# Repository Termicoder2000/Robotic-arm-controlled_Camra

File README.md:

# Robotic Arm Controlled Camera

A Raspberry Pi camera tracks a face and moves a servo-driven robotic arm to keep that face in view. The Raspberry Pi performs camera capture and face detection; an Arduino receives movement commands over I2C and generates the servo PWM signals.

## System Overview

1. The Raspberry Pi captures 640 x 480 camera frames and detects faces with OpenCV.
2. If several faces are visible, it selects the face closest to the previously tracked face.
3. It calculates the selected face's horizontal and vertical offset from the image center.
4. It sends each direction and magnitude to the Arduino over I2C (slave address `0x50`).
5. The Arduino updates hardware timer values to move the servos. A button connected to Raspberry Pi BCM GPIO 21 requests a system shutdown.

### Raspberry Pi Flow

### Arduino Flow

## Why Use an Arduino for Servo PWM?

The Raspberry Pi runs Linux, a multitasking operating system that does not guarantee when a user-space process will run. If software on the Pi bit-bangs servo PWM through GPIO, scheduling delays can shift pulse edges and introduce timing jitter. Servos may respond to that jitter with audible noise, vibration, or imprecise movement.

The Arduino handles the time-critical servo pulses using its hardware timers. Timer peripherals continue producing regular PWM independently of the main program's I2C processing. This separates the Pi's demanding camera and computer-vision work from the precise timing needed to control the servos. The Pi can generate hardware PWM on some pins and configurations, but this project uses the Arduino's timer-driven outputs for servo control.

## Hardware

- Raspberry Pi with a compatible camera module
- Arduino-compatible controller and the servo-control circuit
- Servo-driven robotic arm
- I2C connection between the Raspberry Pi and Arduino
- Momentary shutdown button connected to BCM GPIO 21 and ground

The project photo below shows the custom controller board mounted above the Raspberry Pi.

**Electrical note:** Raspberry Pi GPIO is 3.3 V only. Make sure the I2C bus pull-ups are safe for the Raspberry Pi; use a bidirectional logic-level shifter if the Arduino side pulls the bus up to 5 V. Connect the grounds of both boards.

## Software

The face-tracking program is [`Robotic_arm_controlled_Camera.py`](Robotic_arm_controlled_Camera.py). The Arduino firmware and Atmel Studio project are in [`Arduino_Arm_Conotrol/Roboter_Arm_PWM_SW/`](Arduino_Arm_Conotrol/Roboter_Arm_PWM_SW/).

The Raspberry Pi program requires:

- Raspberry Pi OS with the camera interface enabled
- Python 3
- OpenCV (`cv2`)
- Picamera2
- `smbus2`
- `RPi.GPIO`

Install the Raspberry Pi OS packages for OpenCV, Picamera2, and GPIO using the package manager for your OS release. Install `smbus2` in the Python environment used to run the program. Enable I2C in `raspi-config`, connect the camera and controller, and verify that the Arduino responds at address `0x50` before starting the tracker.

Run the program on the Raspberry Pi with:

```bash
python3 Robotic_arm_controlled_Camera.py
```

Press the shutdown button to request a clean operating-system shutdown. Stopping the script with Ctrl+C also releases the GPIO and closes the camera preview window.

## Notes

- The OpenCV frontal-face Haar cascade is loaded from OpenCV's bundled data directory.
- The camera preview is displayed full-screen. A graphical desktop session is required.
- Servo limits and the mechanical direction of movement depend on the arm and its calibration.
- This project was developed for a specific camera, controller board, and robotic arm; check wiring and servo ranges before powering the motors.

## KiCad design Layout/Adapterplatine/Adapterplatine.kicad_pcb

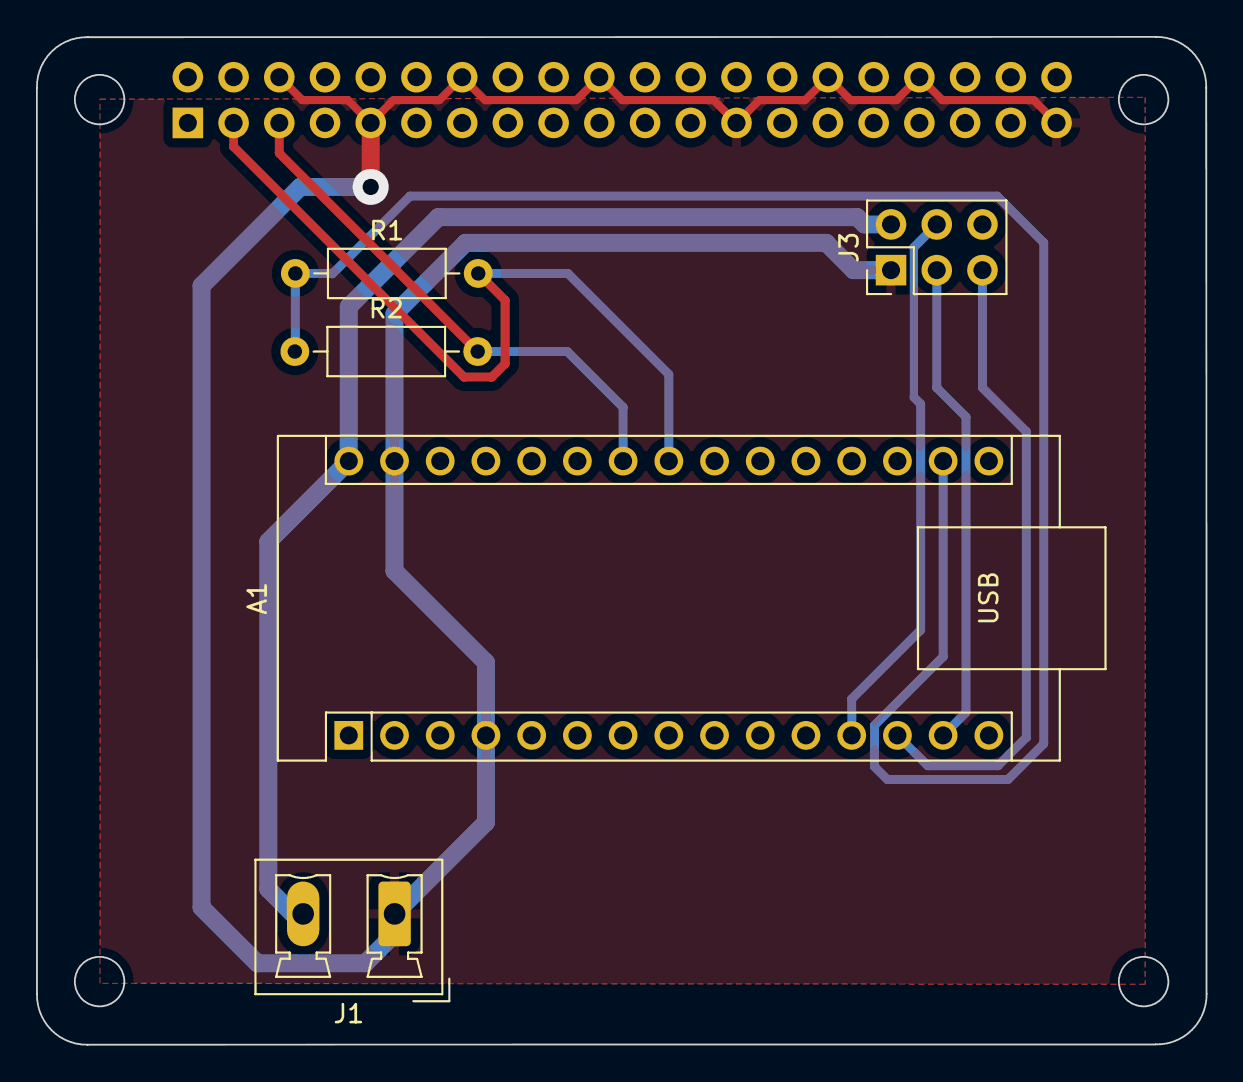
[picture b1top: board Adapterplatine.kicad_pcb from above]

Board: 2 copper layers, 65.0 x 56.0 mm, 6 parts (1 on the bottom side), 8 nets.

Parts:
A1: Arduino_Nano_v3.x; Arduino_Nano
J1: Spannungsversorgung; PhoenixContact_MCV_1,5_2-G-5.08_1x02_P5.08mm_Vertical
J2: raspi Stiftleisten; PinSocket_2x20_P2.54mm_Vertical
J3: Steckerwanne; PinHeader_2x03_P2.54mm_Vertical
R1, R2: 2,2k; R_Axial_DIN0207_L6.3mm_D2.5mm_P10.16mm_Horizontal

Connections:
+5V: A1.30 (VIN), J1.2, J3.2
GND: A1.4 (GND), A1.29 (GND), J1.1, J2.6 (GND), J2.9 (GND), J2.14 (GND), J2.20 (GND), J2.25 (GND), J2.30 (GND), J2.34 (GND), J2.39 (GND), J3.1
unnamed: A1.24 (A5), J2.5 (BCM3), R2.2
unnamed: A1.14 (D11), J3.3
unnamed: A1.12 (D9), J3.4
unnamed: A1.13 (D10), J3.5
unnamed: A1.17 (3V3), R1.1, R2.1
unnamed: A1.23 (A4), J2.3 (BCM2), R1.2
